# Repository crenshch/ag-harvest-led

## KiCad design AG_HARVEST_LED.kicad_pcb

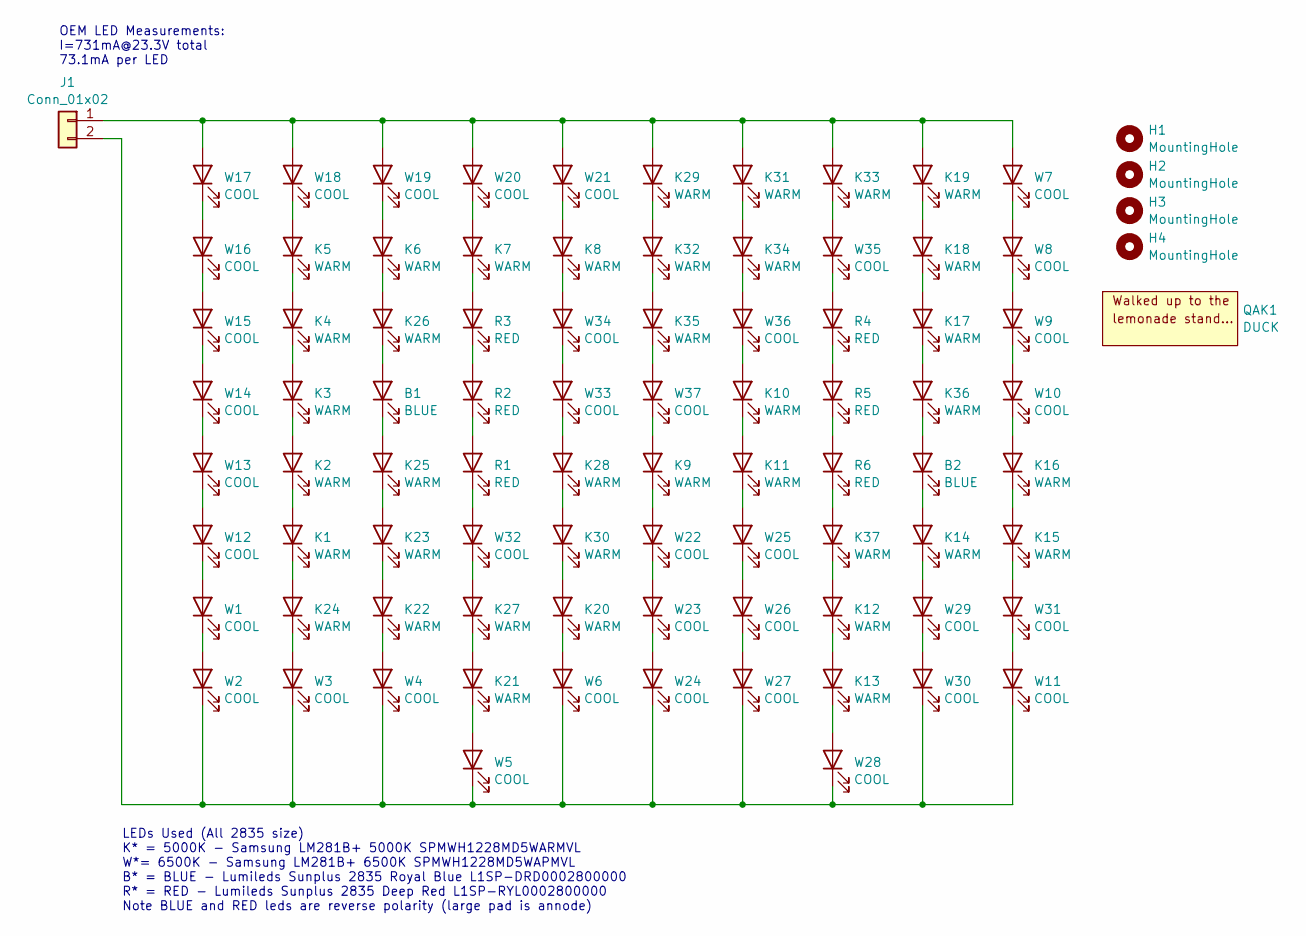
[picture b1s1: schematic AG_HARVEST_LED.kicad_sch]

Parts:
B1, B2: BLUE; Sunplus2835; Mfr. P/N L1SP-RYL0002800000
H1, H2, H3, H4: MountingHole; HOLE_0.25_KEEPOUT_0.45
J1: Conn_01x02; LED_PANNEL_PWR_IN
K1, K2, K3, K4, K5, K6, K7, K8, K9, K10, K11, K12, K13, K14, K15, K16, K17, K18, K19, K20, K21, K22, K23, K24, K25, K26, K27, K28, K29, K30, K31, K32, K33, K34, K35, K36, K37: WARM; LM281B+; Mfr. P/N SPMWH1228MD5WARMVL
QAK1: DUCK; DUCK_cu
R1, R2, R3, R4, R5, R6: RED; Sunplus2835; Mfr. P/N L1SP-DRD0002800000
W1, W2, W3, W4, W5, W6, W7, W8, W9, W10, W11, W12, W13, W14, W15, W16, W17, W18, W19, W20, W21, W22, W23, W24, W25, W26, W27, W28, W29, W30, W31, W32, W33, W34, W35, W36, W37: COOL; LM281B+; Mfr. P/N SPMWH1228MD5WAPMVL

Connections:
unnamed: B1.2 (A), K26.1 (K)
unnamed: B1.1 (K), K25.2 (A)
unnamed: B2.2 (A), K36.1 (K)
unnamed: B2.1 (K), K14.2 (A)
unnamed: J1.1, K19.2 (A), K29.2 (A), K31.2 (A), K33.2 (A), W7.2 (A), W17.2 (A), W18.2 (A), W19.2 (A), W20.2 (A), W21.2 (A)
unnamed: J1.2, W2.1 (K), W3.1 (K), W4.1 (K), W5.1 (K), W6.1 (K), W11.1 (K), W24.1 (K), W27.1 (K), W28.1 (K), W30.1 (K)
unnamed: K1.2 (A), K2.1 (K)
unnamed: K1.1 (K), K24.2 (A)
unnamed: K2.2 (A), K3.1 (K)
unnamed: K3.2 (A), K4.1 (K)
unnamed: K4.2 (A), K5.1 (K)
unnamed: K5.2 (A), W18.1 (K)
unnamed: K6.2 (A), W19.1 (K)
unnamed: K7.2 (A), W20.1 (K)
unnamed: K7.1 (K), R3.2 (A)
unnamed: K8.2 (A), W21.1 (K)
unnamed: K8.1 (K), W34.2 (A)
unnamed: K9.2 (A), W37.1 (K)
unnamed: K9.1 (K), W22.2 (A)
unnamed: K10.2 (A), W36.1 (K)
unnamed: K10.1 (K), K11.2 (A)
unnamed: K11.1 (K), W25.2 (A)
unnamed: K12.2 (A), K37.1 (K)
unnamed: K12.1 (K), K13.2 (A)
unnamed: K13.1 (K), W28.2 (A)
unnamed: K14.1 (K), W29.2 (A)
unnamed: K15.2 (A), K16.1 (K)
unnamed: K15.1 (K), W31.2 (A)
unnamed: K16.2 (A), W10.1 (K)
unnamed: K17.2 (A), K18.1 (K)
unnamed: K17.1 (K), K36.2 (A)
unnamed: K18.2 (A), K19.1 (K)
unnamed: K20.2 (A), K30.1 (K)
unnamed: K20.1 (K), W6.2 (A)
unnamed: K21.2 (A), K27.1 (K)
unnamed: K21.1 (K), W5.2 (A)
unnamed: K22.2 (A), K23.1 (K)
unnamed: K22.1 (K), W4.2 (A)
unnamed: K23.2 (A), K25.1 (K)
unnamed: K24.1 (K), W3.2 (A)
unnamed: K6.1 (K), K26.2 (A)
unnamed: K27.2 (A), W32.1 (K)
unnamed: K28.2 (A), W33.1 (K)
unnamed: K28.1 (K), K30.2 (A)
unnamed: K29.1 (K), K32.2 (A)
unnamed: K31.1 (K), K34.2 (A)
unnamed: K32.1 (K), K35.2 (A)
unnamed: K33.1 (K), W35.2 (A)
unnamed: K34.1 (K), W36.2 (A)
unnamed: K35.1 (K), W37.2 (A)
unnamed: K37.2 (A), R6.1 (K)
unnamed: R1.2 (A), R2.1 (K)
unnamed: R1.1 (K), W32.2 (A)
unnamed: R2.2 (A), R3.1 (K)
unnamed: R4.2 (A), W35.1 (K)
unnamed: R4.1 (K), R5.2 (A)
unnamed: R5.1 (K), R6.2 (A)
unnamed: W1.2 (A), W12.1 (K)
unnamed: W1.1 (K), W2.2 (A)
unnamed: W7.1 (K), W8.2 (A)
unnamed: W8.1 (K), W9.2 (A)
unnamed: W9.1 (K), W10.2 (A)
unnamed: W11.2 (A), W31.1 (K)
unnamed: W12.2 (A), W13.1 (K)
unnamed: W13.2 (A), W14.1 (K)
unnamed: W14.2 (A), W15.1 (K)
unnamed: W15.2 (A), W16.1 (K)
unnamed: W16.2 (A), W17.1 (K)
unnamed: W22.1 (K), W23.2 (A)
unnamed: W23.1 (K), W24.2 (A)
unnamed: W25.1 (K), W26.2 (A)
unnamed: W26.1 (K), W27.2 (A)
unnamed: W29.1 (K), W30.2 (A)
unnamed: W33.2 (A), W34.1 (K)

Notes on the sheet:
OEM LED Measurements: I=731mA@23.3V total 73.1mA per LED
LEDs Used (All 2835 size) K* = 5000K - Samsung LM281B+ 5000K SPMWH1228MD5WARMVL W*= 6500K - Samsung LM281B+ 6500K SPMWH1228MD5WAPMVL B* = BLUE - Lumileds Sunplus 2835 Royal Blue L1SP-DRD0002800000 R* = RED - Lumileds Sunplus 2835 Deep Red L1SP-RYL0002800000 Note BLUE and RED leds are reverse polari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

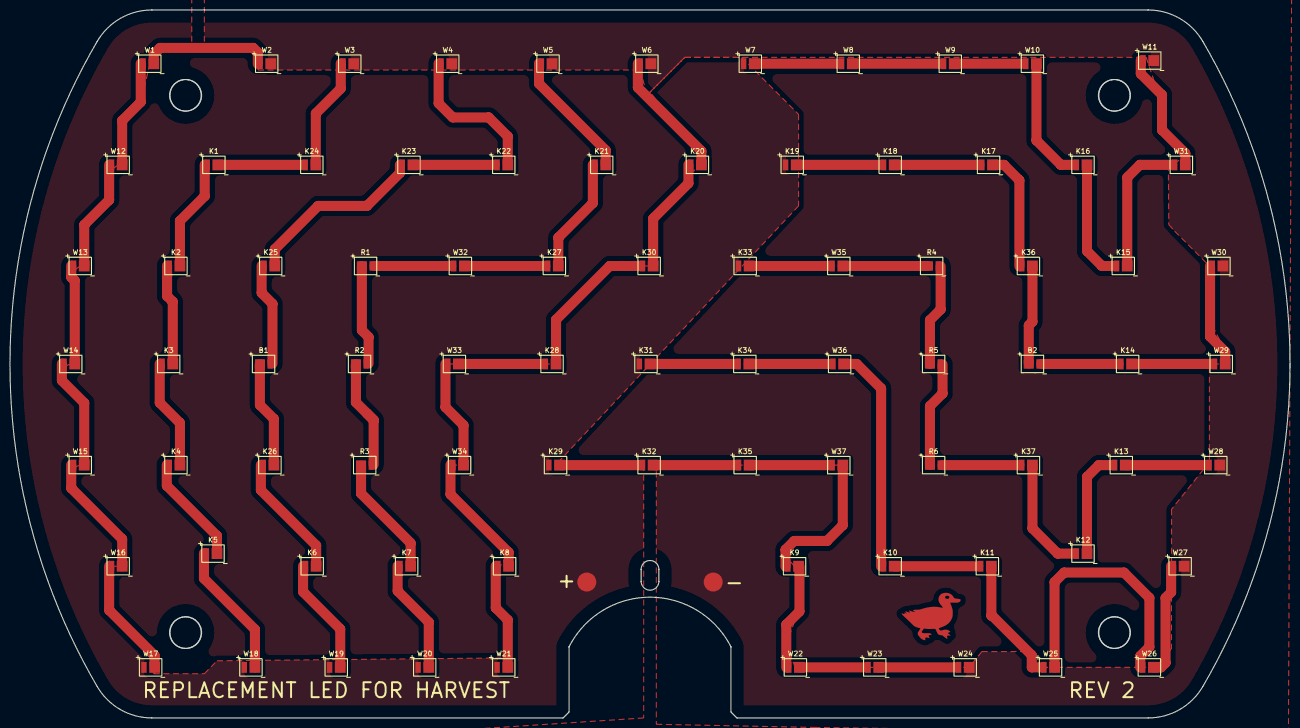
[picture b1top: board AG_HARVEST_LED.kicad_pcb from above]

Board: 2 copper layers, 257.2 x 142.2 mm, 88 parts (1 on the bottom side), 74 nets.

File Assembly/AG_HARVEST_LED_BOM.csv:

"Source:","/home/connor/Sync/Electronics/AG_HARVEST_LED/AG_HARVEST_LED.kicad_sch"
"Date:","Wed 02 Aug 2023 08:48:46 PM EDT"
"Tool:","Eeschema 7.0.6-7.0.6~ubuntu22.04.1"
"Generator:","/usr/share/kicad/plugins/bom_csv_grouped_by_value.py"
"Component Count:","82"

"Collated Components:"

"Item","Qty","Reference(s)","Value","LibPart","Footprint","Datasheet","DNP","Mfr","Mfr. P/N"
"1","2","B1, B2","BLUE","Device:LED","PCB Libraries:Sunplus2835","~","","Lumileds","L1SP-RYL0002800000"
"2","37","K1, K2, K3, K4, K5, K6, K7, K8, K9, K10, K11, K12, K13, K14, K15, K16, K17, K18, K19, K20, K21, K22, K23, K24, K25, K26, K27, K28, K29, K30, K31, K32, K33, K34, K35, K36, K37","WARM","Device:LED","PCB Libraries:LM281B+","~","","Samsung","SPMWH1228MD5WARMVL"
"3","6","R1, R2, R3, R4, R5, R6","RED","Device:LED","PCB Libraries:Sunplus2835","~","","Lumileds","L1SP-DRD0002800000"
"4","37","W1, W2, W3, W4, W5, W6, W7, W8, W9, W10, W11, W12, W13, W14, W15, W16, W17, W18, W19, W20, W21, W22, W23, W24, W25, W26, W27, W28, W29, W30, W31, W32, W33, W34, W35, W36, W37","COOL","Device:LED","PCB Libraries:LM281B+","~","","Samsung","SPMWH1228MD5WAPMVL"
